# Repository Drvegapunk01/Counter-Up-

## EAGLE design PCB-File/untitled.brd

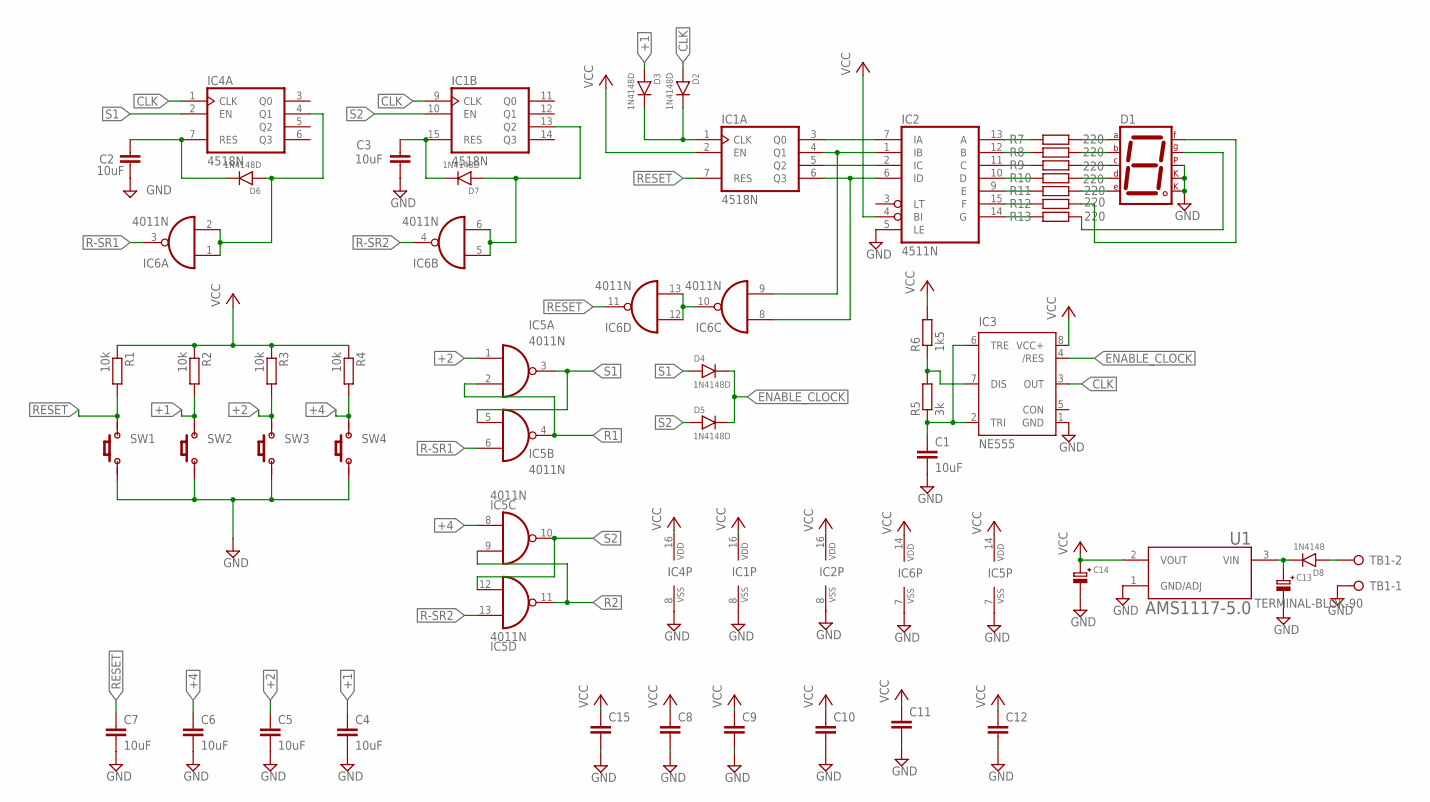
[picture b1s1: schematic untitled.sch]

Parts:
C1, C2, C3, C4, C5, C6, C7: 10uF; SMD0805
C8, C9, C10, C11, C12, C15: CAP-NON; MKM
C13, C14: CAP-ELCO; ELCO1
D1: 7SEG-CK; 7SEG-13
D2, D3, D4, D5, D6, D7: 1N4148D; SOD80C
D8: 1N4148; DIODE
IC1, IC4: 4518N; DIL16
IC2: 4511N; DIL16
IC3: NE555; DIL-08
IC5, IC6: 4011N; DIL14
R1, R2, R3, R4: 10k; SMD0805
R5: 3k; SMD0805
R6: 1k5; SMD0805
R7, R8, R9, R10, R11, R12, R13: 220; SMD0805
SW1, SW2, SW3, SW4: PUSH_BUTTON4P; PUSH_BUTTON_4P
TB1: TERMINAL-BLOK-90; MSTBA2
U1: AMS1117-5.0; SOT229P700X180-4N

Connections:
+1: C4.1, D3.A (1), R2.2, SW2.3 (2), SW2.4 (2)
+2: C5.1, IC5.1 (I0), R3.2, SW3.3 (2), SW3.4 (2)
+4: C6.1, IC5.8 (I0), R4.2, SW4.3 (2), SW4.4 (2)
CLK: D2.A (1), IC1.9 (CLK), IC3.3 (OUT), IC4.1 (CLK)
ENABLE_CLOCK: D4.C (2), D5.C (2), IC3.4 (/RES)
GND: C1.2, C2.2, C3.2, C4.2, C5.2, C6.2, C7.2, C8.2, C9.2, C10.2, C11.2, C12.2, C13.2, C14.2, C15.2, D1.3 (CK1), D1.5 (DP), D1.8 (CK2), IC1.8 (VSS), IC2.5 (LE), IC3.1 (GND), IC4.8 (VSS), IC5.7 (VSS), IC6.7 (VSS), SW1.1, SW1.2 (1), SW2.1, SW2.2 (1), SW3.1, SW3.2 (1), SW4.1, SW4.2 (1), TB1.1, U1.1 (GND/ADJ)
unnamed: IC2.13 (A), R7.1
unnamed: D1.1 (E), R11.2
unnamed: D1.2 (D), R10.2
unnamed: D1.4 (C), R9.2
unnamed: D1.6 (B), R8.2
unnamed: D1.9 (F), R12.2
unnamed: D1.10 (G), R13.2
unnamed: IC1.6 (Q3), IC2.6 (ID), IC6.8 (I0)
unnamed: IC1.5 (Q2), IC2.2 (IC)
unnamed: IC1.4 (Q1), IC2.1 (IB), IC6.9 (I1)
unnamed: IC1.3 (Q0), IC2.7 (IA)
unnamed: C1.1, IC3.2 (TRI), IC3.6 (TRE), R5.1
unnamed: D2.C (2), D3.C (2), IC1.1 (CLK)
unnamed: IC3.7 (DIS), R5.2, R6.1
unnamed: C2.1, D6.C (2), IC4.7 (RES)
unnamed: C3.1, D7.C (2), IC1.15 (RES)
unnamed: D6.A (1), IC4.4 (Q1), IC6.1 (I0), IC6.2 (I1)
unnamed: D7.A (1), IC1.13 (Q2), IC6.5 (I0), IC6.6 (I1)
unnamed: IC6.10 (O), IC6.12 (I0), IC6.13 (I1)
unnamed: D1.7 (A), R7.2
unnamed: IC2.12 (B), R8.1
unnamed: IC2.11 (C), R9.1
unnamed: IC2.10 (D), R10.1
unnamed: IC2.9 (E), R11.1
unnamed: IC2.15 (F), R12.1
unnamed: IC2.14 (G), R13.1
unnamed: C13.1, D8.2, U1.3 (VIN)
unnamed: D8.1, TB1.2
R1: IC5.2 (I1), IC5.4 (O)
R2: IC5.9 (I1), IC5.11 (O)
R-SR1: IC5.6 (I1), IC6.3 (O)
R-SR2: IC5.13 (I1), IC6.4 (O)
RESET: C7.1, IC1.7 (RES), IC6.11 (O), R1.2, SW1.3 (2), SW1.4 (2)
S1: D4.A (1), IC4.2 (EN), IC5.3 (O), IC5.5 (I0)
S2: D5.A (1), IC1.10 (EN), IC5.10 (O), IC5.12 (I0)
VCC: C8.1, C9.1, C10.1, C11.1, C12.1, C14.1, C15.1, IC1.2 (EN), IC1.16 (VDD), IC2.4 (BI), IC2.16 (VDD), IC3.8 (VCC+), IC4.16 (VDD), IC5.14 (VDD), IC6.14 (VDD), R1.1, R2.1, R3.1, R4.1, R6.2, U1.2 (VOUT)
VSS: IC2.8 (VSS)

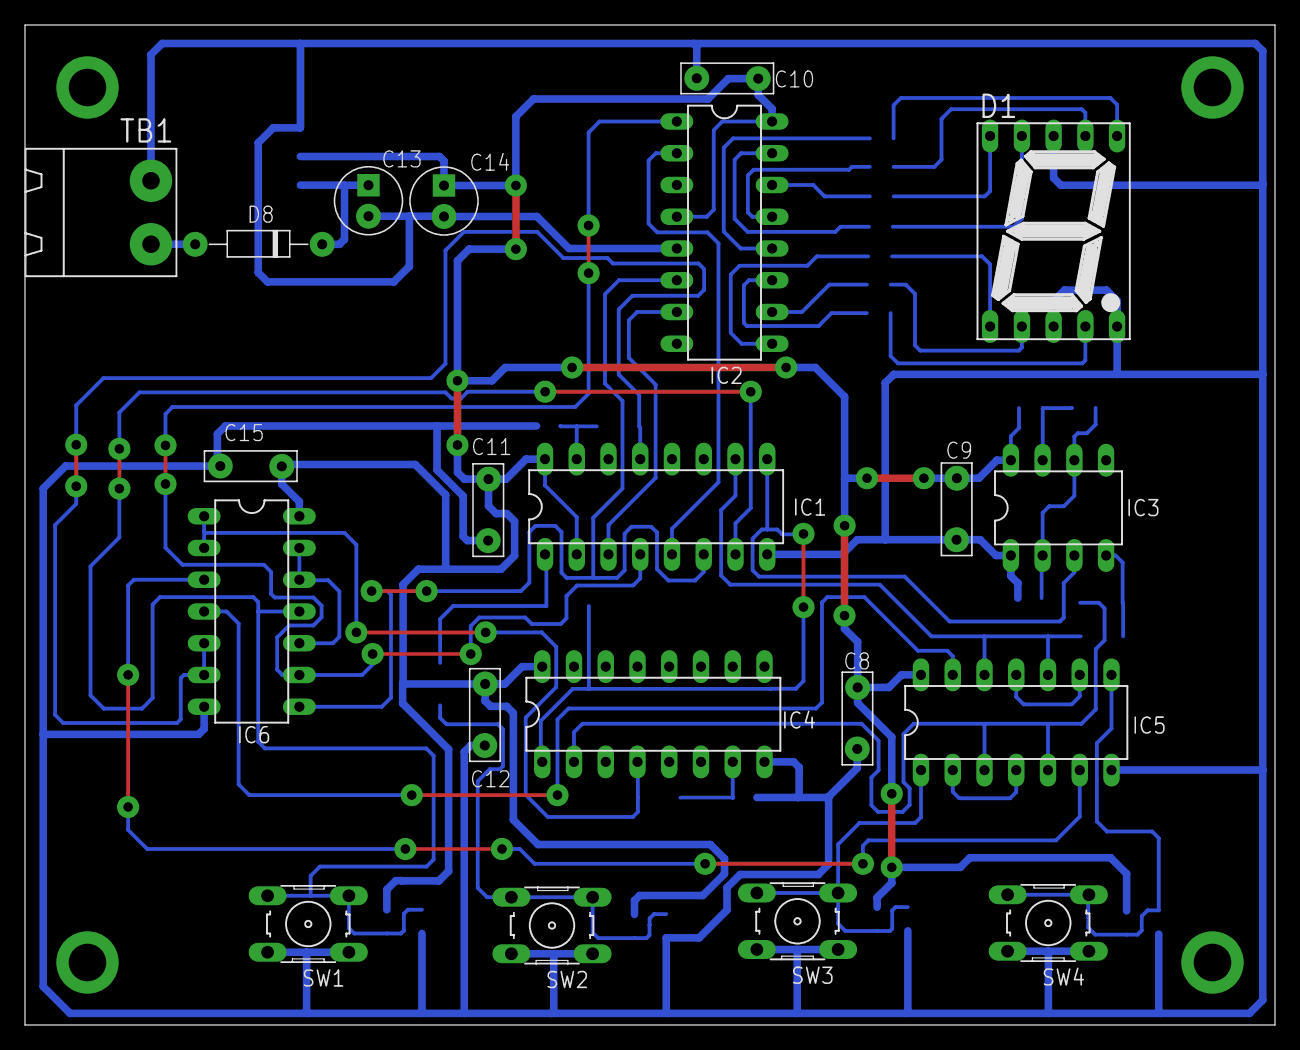
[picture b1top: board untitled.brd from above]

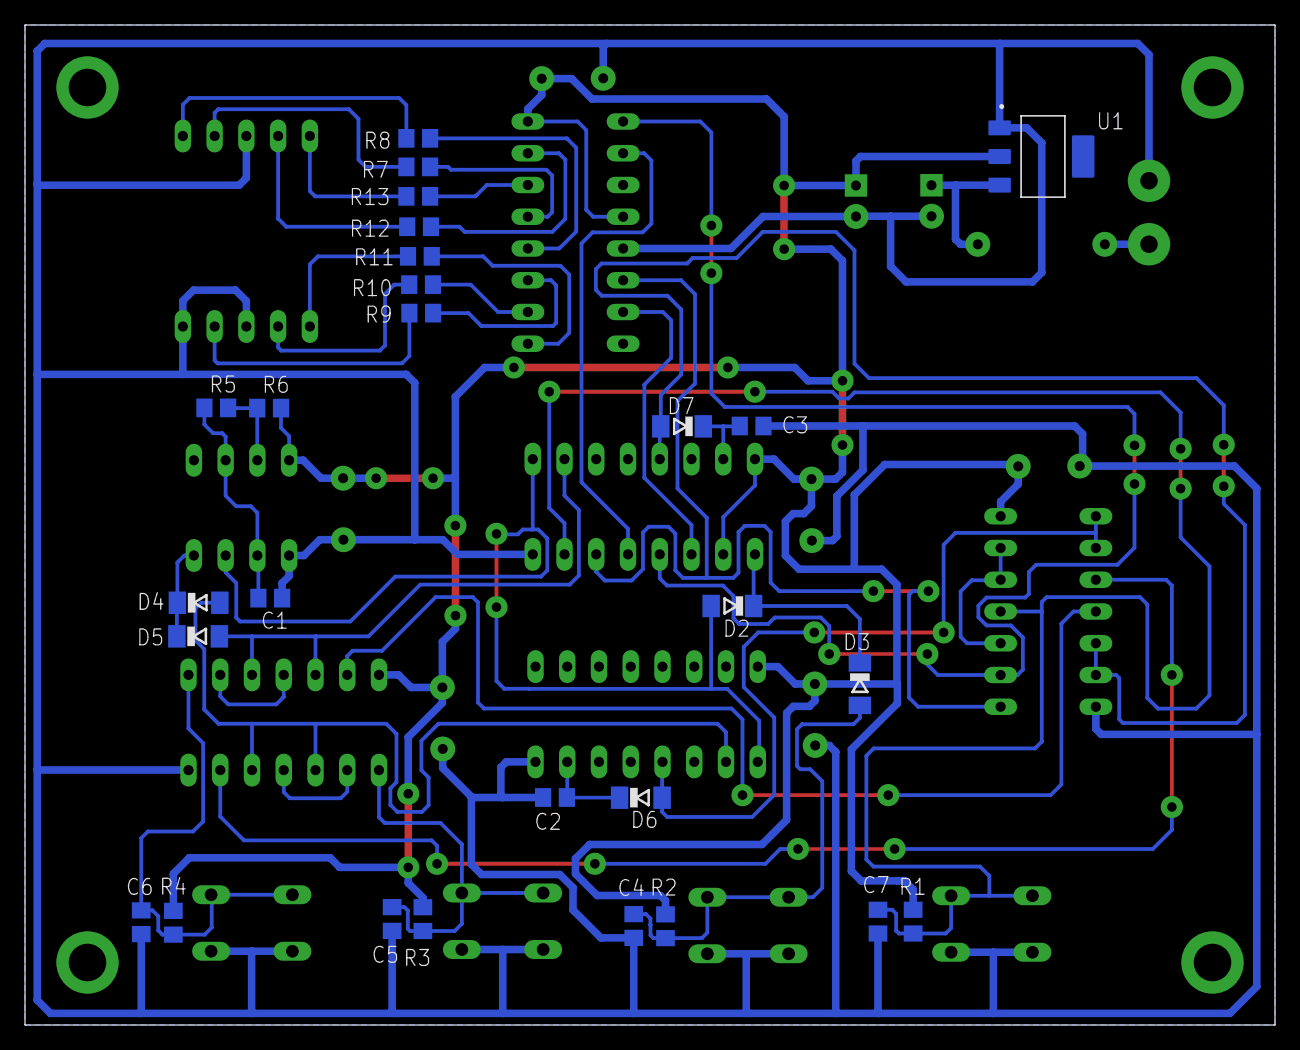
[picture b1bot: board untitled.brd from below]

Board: 2 copper layers, 100.0 x 80.0 mm, 48 parts (27 on the bottom side), 42 nets.

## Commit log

2025-06-14 README
